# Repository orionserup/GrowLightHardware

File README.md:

# GrowLightHardware
 Hardware for the Open Source Grow Light

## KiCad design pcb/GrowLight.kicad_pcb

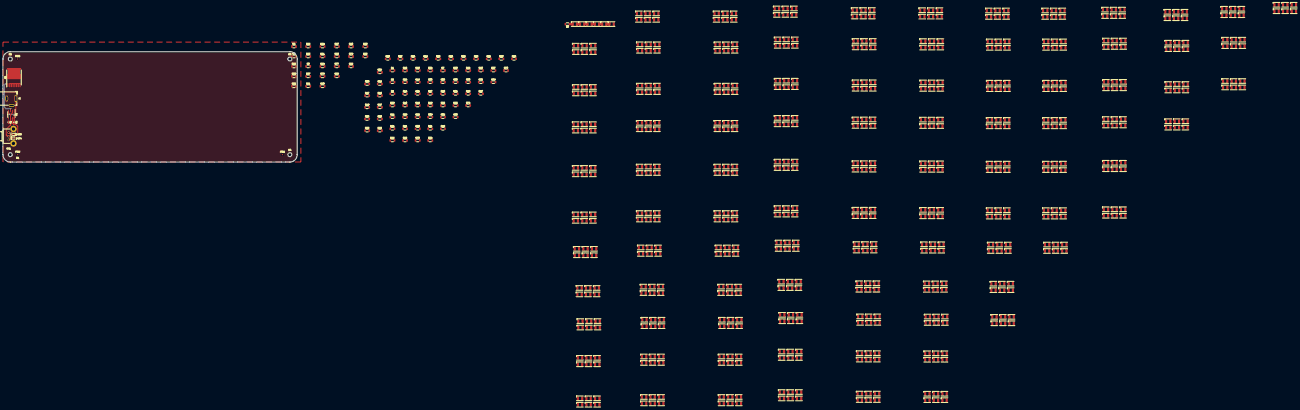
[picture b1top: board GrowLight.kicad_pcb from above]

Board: 2 copper layers, 203.2 x 76.2 mm, 687 parts (0 on the bottom side), 584 nets.

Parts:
C1: 100nF; C_0603_1608Metric
D1, D2, D3, D4, D5, D6, D7, D8, D9, D10, D11, D12, D13, D14, D15, D16, D17, D18, D19, D20, D21, D22, D23, D24, D25, D26, D27, D28, D29, D30, D31, D32, D33, D34, D35, D36, D37, D38, D39, D40, D41, D42, D43, D44, D45, D46, D47, D48, D49, D50, D51, D52, D53, D54, D55, D56, D57, D58, D59, D60, D61, D62, D63, D64, D65, D66, D67, D68, D69, D70, D71, D72, D73, D74, D75, D76, D77, D78, D79, D80, D81, D82, D83, D84, D85, D86, D87, D88, D89, D90, D91, D92, D93, D94, D95, D96, D97, D98, D99, D100, D101, D102, D103, D104, D105, D106, D107, D108, D109, D110, D111, D112, D113, D114, D115, D116, D117, D118, D119, D120, D121, D122, D123, D124, D125, D126, D127, D128, D129, D130, D131, D132, D133, D134, D135, D136, D137, D138, D139, D140, D141, D142, D143, D144, D145, D146, D147, D148, D149, D150, D151, D152, D153, D154, D155, D156, D157, D158, D159, D160, D161, D162, D163, D164, D165, D166, D167, D168, D169, D170, D171, D172, D173, D174, D175, D176, D177, D178, D179, D180, D181, D182, D183, D184, D185, D186, D187, D188, D189, D190, D191, D192, D193, D194, D195, D196, D197, D198, D199, D200, D201, D202, D203, D204, D205, D206, D207, D208, D209, D210, D211, D212, D213, D214, D215, D216, D217, D218, D219, D220, D221, D222, D223, D224, D225, D226, D227, D228, D229, D230, D231, D232, D233, D234, D235, D236, D237, D238, D239, D240, D241, D242, D243, D244, D245, D246, D247, D248, D249, D250, D251, D252, D253, D254, D255, D256, D257, D258, D259, D260, D261, D262, D263, D264, D265, D266, D267, D268, D269, D270, D271, D272, D273, D274, D275, D276, D277, D278, D279, D280, D281, D282, D283, D284, D285, D286, D287, D288, D289, D290, D291, D292, D293, D294, D295, D296, D297, D298, D299, D300, D301, D302, D303, D304, D305, D306, D307, D308, D309, D310, D311, D312, D313, D314, D315, D316, D317, D318, D319, D320, D321, D322, D323, D324, D325, D326, D327, D328, D329, D330, D331, D332, D333, D334, D335, D336, D337, D338, D339, D340, D341, D342, D343, D344, D345, D346, D347, D348, D349, D350, D351, D352, D353, D354, D355, D356, D357, D358, D359, D360, D361, D362, D363, D364, D365, D366, D367, D368, D369, D370, D371, D372, D373, D374, D375, D376, D377, D378, D379, D380, D381, D382, D383, D384, D385, D386, D387, D388, D389, D390, D391, D392, D393, D394, D395, D396, D397, D398, D399, D400, D401, D402, D403, D404, D405, D406, D407, D408, D409, D410, D411, D412, D413, D414, D415, D416, D417, D418, D419, D420, D421, D422, D423, D424, D425, D426, D427, D428, D429, D430, D431, D432, D435, D436, D437, D438, D439, D440, D441, D442, D443, D444, D445, D446, D447, D448, D449, D450, D451, D452, D453, D454, D455, D456, D457, D458, D459, D460, D461, D462, D463, D464, D465, D466, D467, D468, D469, D470, D471, D472, D473, D474, D475, D476, D477, D478, D479, D480, D481, D482, D483, D484, D485, D486, D487, D488, D489, D490, D491, D492, D493, D494, D495, D496, D497, D498, D499, D500, D501, D502, D503, D504, D505, D506, D507, D508, D509, D510, D511, D512, D513, D514, D515, D516, D517, D518, D519, D520, D521, D522, D523, D524, D525, D526, D527, D528, D529, D530, D531, D532, D533, D534, D535, D536, D537, D538, D539, D540, D541, D542, D543, D544, D545, D546, D547, D548, D549, D550, D551, D552, D553, D554, D555, D556, D557, D558, D559, D560, D561, D562, D563, D564, D565, D566, D567, D568, D569, D570, D571, D572, D573, D574, D575, D576, D577, D578: RED; LED_PLCC-2
D433: SD0603S040S0R2; D_0603_1608Metric
D434: D; D_0603_1608Metric
FID1, FID2, FID3: Fiducial; Fiducial_1mm_Mask2mm
H1, H2, H3, H4: MountingHole; MountingHole_2.7mm_M2.5_ISO7380
J1: Barrel_Jack; BarrelJack_GCT_DCJ200-10-A_Horizontal
Q1: IPT012N08N5; Infineon_PG-HSOF-8-1
R1, R3, R4, R5, R6, R7, R8, R9, R10, R11, R12, R13, R14, R15, R16, R17, R18, R19, R20, R21, R22, R23, R24, R25, R26, R27, R28, R29, R30, R31, R32, R33, R34, R35, R36, R37, R38, R39, R40, R41, R42, R43, R44, R45, R46, R47, R48, R49, R50, R51, R52, R53, R54, R55, R56, R57, R58, R59, R60, R61, R62, R63, R64, R65, R66, R67, R68, R69, R70, R71, R72, R73, R74, R75, R76, R77, R78, R79, R80, R81, R82, R83, R84, R85, R86, R87, R88, R89, R90, R91, R92, R93, R94, R95, R96, R97: 20; R_1206_3216Metric
R2: 1k; R_0603_1608Metric
RV1: 10k; Potentiometer_Bourns_PTV09A-2_Single_Horizontal
U1: LM555xM; SOIC-8_3.9x4.9mm_P1.27mm

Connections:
/Control Circuitry/CTRL: Q1.1 (G), U1.3 (Q)
/Control Circuitry/THR: C1.1, RV1.2, U1.2 (TR), U1.6 (THR)
/LED Grid/CATHODE: Q1.3 (D), R1.2, R3.2, R4.2, R5.2, R6.2, R7.2, R8.2, R9.2, R10.2, R11.2, R12.2, R13.2, R14.2, R15.2, R16.2, R17.2, R18.2, R19.2, R20.2, R21.2, R22.2, R23.2, R24.2, R25.2, R26.2, R27.2, R28.2, R29.2, R30.2, R31.2, R32.2, R33.2, R34.2, R35.2, R36.2, R37.2, R38.2, R39.2, R40.2, R41.2, R42.2, R43.2, R44.2, R45.2, R46.2, R47.2, R48.2, R49.2, R50.2, R51.2, R52.2, R53.2, R54.2, R55.2, R56.2, R57.2, R58.2, R59.2, R60.2, R61.2, R62.2, R63.2, R64.2, R65.2, R66.2, R67.2, R68.2, R69.2, R70.2, R71.2, R72.2, R73.2, R74.2, R75.2, R76.2, R77.2, R78.2, R79.2, R80.2, R81.2, R82.2, R83.2, R84.2, R85.2, R86.2, R87.2, R88.2, R89.2, R90.2, R91.2, R92.2, R93.2, R94.2, R95.2, R96.2, R97.2
/V_{LED}: D1.2 (A), D7.2 (A), D13.2 (A), D19.2 (A), D25.2 (A), D31.2 (A), D37.2 (A), D43.2 (A), D49.2 (A), D55.2 (A), D61.2 (A), D67.2 (A), D73.2 (A), D79.2 (A), D85.2 (A), D91.2 (A), D97.2 (A), D103.2 (A), D109.2 (A), D115.2 (A), D121.2 (A), D127.2 (A), D133.2 (A), D139.2 (A), D145.2 (A), D151.2 (A), D157.2 (A), D163.2 (A), D169.2 (A), D175.2 (A), D181.2 (A), D187.2 (A), D193.2 (A), D199.2 (A), D205.2 (A), D211.2 (A), D217.2 (A), D223.2 (A), D229.2 (A), D235.2 (A), D241.2 (A), D247.2 (A), D253.2 (A), D259.2 (A), D265.2 (A), D271.2 (A), D277.2 (A), D283.2 (A), D289.2 (A), D295.2 (A), D301.2 (A), D307.2 (A), D313.2 (A), D319.2 (A), D325.2 (A), D331.2 (A), D337.2 (A), D343.2 (A), D349.2 (A), D355.2 (A), D361.2 (A), D367.2 (A), D373.2 (A), D379.2 (A), D385.2 (A), D391.2 (A), D397.2 (A), D403.2 (A), D409.2 (A), D415.2 (A), D421.2 (A), D427.2 (A), D435.2 (A), D441.2 (A), D447.2 (A), D453.2 (A), D459.2 (A), D465.2 (A), D471.2 (A), D477.2 (A), D483.2 (A), D489.2 (A), D495.2 (A), D501.2 (A), D507.2 (A), D513.2 (A), D519.2 (A), D525.2 (A), D531.2 (A), D537.2 (A), D543.2 (A), D549.2 (A), D555.2 (A), D561.2 (A), D567.2 (A), D573.2 (A), J1.1, R2.1, U1.4 (R), U1.8 (VCC)
Earth: C1.2, J1.2, Q1.2 (S), U1.1 (GND)
unnamed: D1.1 (K), D2.2 (A)
unnamed: D2.1 (K), D3.2 (A)
unnamed: D3.1 (K), D4.2 (A)
unnamed: D4.1 (K), D5.2 (A)
unnamed: D5.1 (K), D6.2 (A)
unnamed: D6.1 (K), R1.1
unnamed: D7.1 (K), D8.2 (A)
unnamed: D8.1 (K), D9.2 (A)
unnamed: D10.1 (K), D11.2 (A)
unnamed: D9.1 (K), D10.2 (A)
unnamed: D11.1 (K), D12.2 (A)
unnamed: D12.1 (K), R3.1
unnamed: D13.1 (K), D14.2 (A)
unnamed: D14.1 (K), D15.2 (A)
unnamed: D15.1 (K), D16.2 (A)
unnamed: D16.1 (K), D17.2 (A)
unnamed: D17.1 (K), D18.2 (A)
unnamed: D18.1 (K), R4.1
unnamed: D19.1 (K), D20.2 (A)
unnamed: D20.1 (K), D21.2 (A)
unnamed: D21.1 (K), D22.2 (A)
unnamed: D22.1 (K), D23.2 (A)
unnamed: D23.1 (K), D24.2 (A)
unnamed: D24.1 (K), R5.1
unnamed: D25.1 (K), D26.2 (A)
unnamed: D26.1 (K), D27.2 (A)
unnamed: D27.1 (K), D28.2 (A)
unnamed: D28.1 (K), D29.2 (A)
unnamed: D29.1 (K), D30.2 (A)
unnamed: D30.1 (K), R6.1
unnamed: D31.1 (K), D32.2 (A)
unnamed: D32.1 (K), D33.2 (A)
unnamed: D33.1 (K), D34.2 (A)
unnamed: D34.1 (K), D35.2 (A)
unnamed: D35.1 (K), D36.2 (A)
unnamed: D36.1 (K), R7.1
unnamed: D37.1 (K), D38.2 (A)
unnamed: D38.1 (K), D39.2 (A)
unnamed: D39.1 (K), D40.2 (A)
unnamed: D40.1 (K), D41.2 (A)
unnamed: D41.1 (K), D42.2 (A)
unnamed: D42.1 (K), R8.1
unnamed: D43.1 (K), D44.2 (A)
unnamed: D44.1 (K), D45.2 (A)
unnamed: D45.1 (K), D46.2 (A)
unnamed: D46.1 (K), D47.2 (A)
unnamed: D47.1 (K), D48.2 (A)
unnamed: D48.1 (K), R9.1
unnamed: D49.1 (K), D50.2 (A)
unnamed: D50.1 (K), D51.2 (A)
unnamed: D51.1 (K), D52.2 (A)
unnamed: D52.1 (K), D53.2 (A)
unnamed: D53.1 (K), D54.2 (A)
unnamed: D54.1 (K), R10.1
unnamed: D55.1 (K), D56.2 (A)
unnamed: D56.1 (K), D57.2 (A)
unnamed: D57.1 (K), D58.2 (A)
unnamed: D58.1 (K), D59.2 (A)
unnamed: D59.1 (K), D60.2 (A)
unnamed: D60.1 (K), R11.1
unnamed: D61.1 (K), D62.2 (A)
unnamed: D62.1 (K), D63.2 (A)
unnamed: D63.1 (K), D64.2 (A)
unnamed: D64.1 (K), D65.2 (A)
unnamed: D65.1 (K), D66.2 (A)
unnamed: D66.1 (K), R12.1
unnamed: D67.1 (K), D68.2 (A)
unnamed: D68.1 (K), D69.2 (A)
unnamed: D69.1 (K), D70.2 (A)
unnamed: D70.1 (K), D71.2 (A)
unnamed: D71.1 (K), D72.2 (A)
unnamed: D72.1 (K), R13.1
unnamed: D73.1 (K), D74.2 (A)
unnamed: D74.1 (K), D75.2 (A)
unnamed: D75.1 (K), D76.2 (A)
unnamed: D76.1 (K), D77.2 (A)
unnamed: D77.1 (K), D78.2 (A)
unnamed: D78.1 (K), R14.1
unnamed: D79.1 (K), D80.2 (A)
unnamed: D80.1 (K), D81.2 (A)
unnamed: D81.1 (K), D82.2 (A)
unnamed: D82.1 (K), D83.2 (A)
unnamed: D83.1 (K), D84.2 (A)
unnamed: D84.1 (K), R15.1
unnamed: D85.1 (K), D86.2 (A)
unnamed: D86.1 (K), D87.2 (A)
unnamed: D87.1 (K), D88.2 (A)
unnamed: D88.1 (K), D89.2 (A)
unnamed: D89.1 (K), D90.2 (A)
unnamed: D90.1 (K), R16.1
unnamed: D91.1 (K), D92.2 (A)
unnamed: D92.1 (K), D93.2 (A)
unnamed: D93.1 (K), D94.2 (A)
unnamed: D94.1 (K), D95.2 (A)
unnamed: D95.1 (K), D96.2 (A)
unnamed: D96.1 (K), R17.1
unnamed: D97.1 (K), D98.2 (A)
unnamed: D98.1 (K), D99.2 (A)
unnamed: D100.1 (K), D101.2 (A)
unnamed: D99.1 (K), D100.2 (A)
unnamed: D101.1 (K), D102.2 (A)
unnamed: D102.1 (K), R18.1
unnamed: D103.1 (K), D104.2 (A)
unnamed: D104.1 (K), D105.2 (A)
unnamed: D105.1 (K), D106.2 (A)
unnamed: D106.1 (K), D107.2 (A)
unnamed: D107.1 (K), D108.2 (A)
unnamed: D108.1 (K), R19.1
unnamed: D109.1 (K), D110.2 (A)
unnamed: D110.1 (K), D111.2 (A)
unnamed: D111.1 (K), D112.2 (A)
unnamed: D112.1 (K), D113.2 (A)
unnamed: D113.1 (K), D114.2 (A)
unnamed: D114.1 (K), R20.1
unnamed: D115.1 (K), D116.2 (A)
unnamed: D116.1 (K), D117.2 (A)
unnamed: D117.1 (K), D118.2 (A)
unnamed: D118.1 (K), D119.2 (A)
unnamed: D119.1 (K), D120.2 (A)
unnamed: D120.1 (K), R21.1
unnamed: D121.1 (K), D122.2 (A)
unnamed: D122.1 (K), D123.2 (A)
unnamed: D123.1 (K), D124.2 (A)
unnamed: D124.1 (K), D125.2 (A)
unnamed: D125.1 (K), D126.2 (A)
unnamed: D126.1 (K), R22.1
unnamed: D127.1 (K), D128.2 (A)
unnamed: D128.1 (K), D129.2 (A)
unnamed: D129.1 (K), D130.2 (A)
unnamed: D130.1 (K), D131.2 (A)
unnamed: D131.1 (K), D132.2 (A)
unnamed: D132.1 (K), R23.1
unnamed: D133.1 (K), D134.2 (A)
unnamed: D134.1 (K), D135.2 (A)
unnamed: D135.1 (K), D136.2 (A)
unnamed: D136.1 (K), D137.2 (A)
unnamed: D137.1 (K), D138.2 (A)
unnamed: D138.1 (K), R24.1
unnamed: D139.1 (K), D140.2 (A)
unnamed: D140.1 (K), D141.2 (A)
unnamed: D141.1 (K), D142.2 (A)
unnamed: D142.1 (K), D143.2 (A)
unnamed: D143.1 (K), D144.2 (A)
unnamed: D144.1 (K), R25.1
unnamed: D145.1 (K), D146.2 (A)
unnamed: D146.1 (K), D147.2 (A)
unnamed: D147.1 (K), D148.2 (A)
unnamed: D148.1 (K), D149.2 (A)
unnamed: D149.1 (K), D150.2 (A)
unnamed: D150.1 (K), R26.1
unnamed: D151.1 (K), D152.2 (A)
unnamed: D152.1 (K), D153.2 (A)
unnamed: D153.1 (K), D154.2 (A)
unnamed: D154.1 (K), D155.2 (A)
unnamed: D155.1 (K), D156.2 (A)
unnamed: D156.1 (K), R27.1
unnamed: D157.1 (K), D158.2 (A)
unnamed: D158.1 (K), D159.2 (A)
unnamed: D159.1 (K), D160.2 (A)
unnamed: D160.1 (K), D161.2 (A)
unnamed: D161.1 (K), D162.2 (A)
unnamed: D162.1 (K), R28.1
unnamed: D163.1 (K), D164.2 (A)
unnamed: D164.1 (K), D165.2 (A)
unnamed: D165.1 (K), D166.2 (A)
unnamed: D166.1 (K), D167.2 (A)
unnamed: D167.1 (K), D168.2 (A)
unnamed: D168.1 (K), R29.1
unnamed: D169.1 (K), D170.2 (A)
unnamed: D170.1 (K), D171.2 (A)
unnamed: D171.1 (K), D172.2 (A)
unnamed: D172.1 (K), D173.2 (A)
unnamed: D173.1 (K), D174.2 (A)
unnamed: D174.1 (K), R30.1
unnamed: D175.1 (K), D176.2 (A)
unnamed: D176.1 (K), D177.2 (A)
unnamed: D177.1 (K), D178.2 (A)
unnamed: D178.1 (K), D179.2 (A)
unnamed: D179.1 (K), D180.2 (A)
unnamed: D180.1 (K), R31.1
unnamed: D181.1 (K), D182.2 (A)
unnamed: D182.1 (K), D183.2 (A)
unnamed: D183.1 (K), D184.2 (A)
unnamed: D184.1 (K), D185.2 (A)
unnamed: D185.1 (K), D186.2 (A)
unnamed: D186.1 (K), R32.1
unnamed: D187.1 (K), D188.2 (A)
unnamed: D188.1 (K), D189.2 (A)
unnamed: D189.1 (K), D190.2 (A)
unnamed: D190.1 (K), D191.2 (A)
unnamed: D191.1 (K), D192.2 (A)
unnamed: D192.1 (K), R33.1
unnamed: D193.1 (K), D194.2 (A)
unnamed: D194.1 (K), D195.2 (A)
unnamed: D195.1 (K), D196.2 (A)
unnamed: D196.1 (K), D197.2 (A)
unnamed: D197.1 (K), D198.2 (A)
unnamed: D198.1 (K), R34.1
unnamed: D199.1 (K), D200.2 (A)
unnamed: D200.1 (K), D201.2 (A)
unnamed: D201.1 (K), D202.2 (A)
unnamed: D202.1 (K), D203.2 (A)
unnamed: D203.1 (K), D204.2 (A)
unnamed: D204.1 (K), R35.1
unnamed: D205.1 (K), D206.2 (A)
unnamed: D206.1 (K), D207.2 (A)
unnamed: D207.1 (K), D208.2 (A)
unnamed: D208.1 (K), D209.2 (A)
unnamed: D209.1 (K), D210.2 (A)
unnamed: D210.1 (K), R36.1
unnamed: D211.1 (K), D212.2 (A)
unnamed: D212.1 (K), D213.2 (A)
unnamed: D213.1 (K), D214.2 (A)
unnamed: D214.1 (K), D215.2 (A)
unnamed: D215.1 (K), D216.2 (A)
unnamed: D216.1 (K), R37.1
unnamed: D217.1 (K), D218.2 (A)
unnamed: D218.1 (K), D219.2 (A)
unnamed: D219.1 (K), D220.2 (A)
unnamed: D220.1 (K), D221.2 (A)
unnamed: D221.1 (K), D222.2 (A)
unnamed: D222.1 (K), R38.1
unnamed: D223.1 (K), D224.2 (A)
unnamed: D224.1 (K), D225.2 (A)
unnamed: D225.1 (K), D226.2 (A)
unnamed: D226.1 (K), D227.2 (A)
unnamed: D227.1 (K), D228.2 (A)
unnamed: D228.1 (K), R39.1
unnamed: D229.1 (K), D230.2 (A)
unnamed: D230.1 (K), D231.2 (A)
unnamed: D231.1 (K), D232.2 (A)
unnamed: D232.1 (K), D233.2 (A)
unnamed: D233.1 (K), D234.2 (A)
unnamed: D234.1 (K), R40.1
unnamed: D235.1 (K), D236.2 (A)
unnamed: D236.1 (K), D237.2 (A)
unnamed: D237.1 (K), D238.2 (A)
unnamed: D238.1 (K), D239.2 (A)
unnamed: D239.1 (K), D240.2 (A)
unnamed: D240.1 (K), R41.1
unnamed: D241.1 (K), D242.2 (A)
unnamed: D242.1 (K), D243.2 (A)
unnamed: D243.1 (K), D244.2 (A)
unnamed: D244.1 (K), D245.2 (A)
unnamed: D245.1 (K), D246.2 (A)
unnamed: D246.1 (K), R42.1
unnamed: D247.1 (K), D248.2 (A)
unnamed: D248.1 (K), D249.2 (A)
unnamed: D249.1 (K), D250.2 (A)
unnamed: D250.1 (K), D251.2 (A)
unnamed: D251.1 (K), D252.2 (A)
unnamed: D252.1 (K), R43.1
unnamed: D253.1 (K), D254.2 (A)
unnamed: D254.1 (K), D255.2 (A)
unnamed: D255.1 (K), D256.2 (A)
unnamed: D256.1 (K), D257.2 (A)
unnamed: D257.1 (K), D258.2 (A)
unnamed: D258.1 (K), R44.1
unnamed: D259.1 (K), D260.2 (A)
unnamed: D260.1 (K), D261.2 (A)
unnamed: D261.1 (K), D262.2 (A)
unnamed: D262.1 (K), D263.2 (A)
unnamed: D263.1 (K), D264.2 (A)
unnamed: D264.1 (K), R45.1
unnamed: D265.1 (K), D266.2 (A)
unnamed: D266.1 (K), D267.2 (A)
unnamed: D267.1 (K), D268.2 (A)
unnamed: D268.1 (K), D269.2 (A)
unnamed: D269.1 (K), D270.2 (A)
unnamed: D270.1 (K), R46.1
unnamed: D271.1 (K), D272.2 (A)
unnamed: D272.1 (K), D273.2 (A)
unnamed: D273.1 (K), D274.2 (A)
unnamed: D274.1 (K), D275.2 (A)
unnamed: D275.1 (K), D276.2 (A)
unnamed: D276.1 (K), R47.1
unnamed: D277.1 (K), D278.2 (A)
unnamed: D278.1 (K), D279.2 (A)
unnamed: D279.1 (K), D280.2 (A)
unnamed: D280.1 (K), D281.2 (A)
unnamed: D281.1 (K), D282.2 (A)
unnamed: D282.1 (K), R48.1
unnamed: D283.1 (K), D284.2 (A)
unnamed: D284.1 (K), D285.2 (A)
unnamed: D285.1 (K), D286.2 (A)
unnamed: D286.1 (K), D287.2 (A)
unnamed: D287.1 (K), D288.2 (A)
unnamed: D288.1 (K), R49.1
unnamed: D289.1 (K), D290.2 (A)
unnamed: D290.1 (K), D291.2 (A)
unnamed: D291.1 (K), D292.2 (A)
unnamed: D292.1 (K), D293.2 (A)
unnamed: D293.1 (K), D294.2 (A)
unnamed: D294.1 (K), R50.1
unnamed: D295.1 (K), D296.2 (A)
unnamed: D296.1 (K), D297.2 (A)
unnamed: D297.1 (K), D298.2 (A)
unnamed: D298.1 (K), D299.2 (A)
unnamed: D299.1 (K), D300.2 (A)
unnamed: D300.1 (K), R51.1
unnamed: D301.1 (K), D302.2 (A)
unnamed: D302.1 (K), D303.2 (A)
unnamed: D303.1 (K), D304.2 (A)
unnamed: D304.1 (K), D305.2 (A)
unnamed: D305.1 (K), D306.2 (A)
unnamed: D306.1 (K), R52.1
unnamed: D307.1 (K), D308.2 (A)
unnamed: D308.1 (K), D309.2 (A)
unnamed: D309.1 (K), D310.2 (A)
unnamed: D310.1 (K), D311.2 (A)
unnamed: D311.1 (K), D312.2 (A)
unnamed: D312.1 (K), R53.1
unnamed: D313.1 (K), D314.2 (A)
unnamed: D314.1 (K), D315.2 (A)
unnamed: D315.1 (K), D316.2 (A)
unnamed: D316.1 (K), D317.2 (A)
unnamed: D317.1 (K), D318.2 (A)
unnamed: D318.1 (K), R54.1
unnamed: D319.1 (K), D320.2 (A)
unnamed: D320.1 (K), D321.2 (A)
unnamed: D321.1 (K), D322.2 (A)
unnamed: D322.1 (K), D323.2 (A)
unnamed: D323.1 (K), D324.2 (A)
unnamed: D324.1 (K), R55.1
unnamed: D325.1 (K), D326.2 (A)
unnamed: D326.1 (K), D327.2 (A)
unnamed: D327.1 (K), D328.2 (A)
unnamed: D328.1 (K), D329.2 (A)
unnamed: D329.1 (K), D330.2 (A)
unnamed: D330.1 (K), R56.1
unnamed: D331.1 (K), D332.2 (A)
unnamed: D332.1 (K), D333.2 (A)
unnamed: D333.1 (K), D334.2 (A)
unnamed: D334.1 (K), D335.2 (A)
unnamed: D335.1 (K), D336.2 (A)
unnamed: D336.1 (K), R57.1
unnamed: D337.1 (K), D338.2 (A)
unnamed: D338.1 (K), D339.2 (A)
unnamed: D339.1 (K), D340.2 (A)
unnamed: D340.1 (K), D341.2 (A)
unnamed: D341.1 (K), D342.2 (A)
unnamed: D342.1 (K), R58.1
unnamed: D343.1 (K), D344.2 (A)
unnamed: D344.1 (K), D345.2 (A)
unnamed: D345.1 (K), D346.2 (A)
unnamed: D346.1 (K), D347.2 (A)
unnamed: D347.1 (K), D348.2 (A)
unnamed: D348.1 (K), R59.1
unnamed: D349.1 (K), D350.2 (A)
unnamed: D350.1 (K), D351.2 (A)
unnamed: D351.1 (K), D352.2 (A)
unnamed: D352.1 (K), D353.2 (A)
unnamed: D353.1 (K), D354.2 (A)
unnamed: D354.1 (K), R60.1
unnamed: D355.1 (K), D356.2 (A)
unnamed: D356.1 (K), D357.2 (A)
unnamed: D357.1 (K), D358.2 (A)
unnamed: D358.1 (K), D359.2 (A)
unnamed: D359.1 (K), D360.2 (A)
unnamed: D360.1 (K), R61.1
unnamed: D361.1 (K), D362.2 (A)
unnamed: D362.1 (K), D363.2 (A)
unnamed: D363.1 (K), D364.2 (A)
unnamed: D364.1 (K), D365.2 (A)
unnamed: D365.1 (K), D366.2 (A)
unnamed: D366.1 (K), R62.1
unnamed: D367.1 (K), D368.2 (A)
unnamed: D368.1 (K), D369.2 (A)
unnamed: D369.1 (K), D370.2 (A)
unnamed: D370.1 (K), D371.2 (A)
unnamed: D371.1 (K), D372.2 (A)
unnamed: D372.1 (K), R63.1
unnamed: D373.1 (K), D374.2 (A)
unnamed: D374.1 (K), D375.2 (A)
unnamed: D375.1 (K), D376.2 (A)
unnamed: D376.1 (K), D377.2 (A)
unnamed: D377.1 (K), D378.2 (A)
unnamed: D378.1 (K), R64.1
unnamed: D379.1 (K), D380.2 (A)
unnamed: D380.1 (K), D381.2 (A)
unnamed: D381.1 (K), D382.2 (A)
unnamed: D382.1 (K), D383.2 (A)
unnamed: D383.1 (K), D384.2 (A)
unnamed: D384.1 (K), R65.1
unnamed: D385.1 (K), D386.2 (A)
unnamed: D386.1 (K), D387.2 (A)
unnamed: D387.1 (K), D388.2 (A)
unnamed: D388.1 (K), D389.2 (A)
unnamed: D389.1 (K), D390.2 (A)
unnamed: D390.1 (K), R66.1
unnamed: D391.1 (K), D392.2 (A)
unnamed: D392.1 (K), D393.2 (A)
unnamed: D393.1 (K), D394.2 (A)
unnamed: D394.1 (K), D395.2 (A)
unnamed: D395.1 (K), D396.2 (A)
unnamed: D396.1 (K), R67.1
unnamed: D397.1 (K), D398.2 (A)
unnamed: D398.1 (K), D399.2 (A)
unnamed: D399.1 (K), D400.2 (A)
unnamed: D400.1 (K), D401.2 (A)
unnamed: D401.1 (K), D402.2 (A)
unnamed: D402.1 (K), R68.1
unnamed: D403.1 (K), D404.2 (A)
unnamed: D404.1 (K), D405.2 (A)
unnamed: D405.1 (K), D406.2 (A)
unnamed: D406.1 (K), D407.2 (A)
unnamed: D407.1 (K), D408.2 (A)
unnamed: D408.1 (K), R69.1
unnamed: D409.1 (K), D410.2 (A)
unnamed: D410.1 (K), D411.2 (A)
unnamed: D411.1 (K), D412.2 (A)
unnamed: D412.1 (K), D413.2 (A)
unnamed: D413.1 (K), D414.2 (A)
unnamed: D414.1 (K), R70.1
unnamed: D415.1 (K), D416.2 (A)
unnamed: D416.1 (K), D417.2 (A)
unnamed: D417.1 (K), D418.2 (A)
unnamed: D418.1 (K), D419.2 (A)
unnamed: D419.1 (K), D420.2 (A)
unnamed: D420.1 (K), R71.1
unnamed: D421.1 (K), D422.2 (A)
unnamed: D422.1 (K), D423.2 (A)
unnamed: D423.1 (K), D424.2 (A)
unnamed: D424.1 (K), D425.2 (A)
unnamed: D425.1 (K), D426.2 (A)
unnamed: D426.1 (K), R72.1
unnamed: D427.1 (K), D428.2 (A)
unnamed: D428.1 (K), D429.2 (A)
unnamed: D429.1 (K), D430.2 (A)
unnamed: D430.1 (K), D431.2 (A)
unnamed: D431.1 (K), D432.2 (A)
unnamed: D432.1 (K), R73.1
unnamed: D433.1 (K), RV1.3
unnamed: D433.2 (A), D434.1 (K), R2.2, U1.7 (DIS)
unnamed: D434.2 (A), RV1.1
unnamed: D435.1 (K), D436.2 (A)
unnamed: D436.1 (K), D437.2 (A)
unnamed: D437.1 (K), D438.2 (A)
unnamed: D438.1 (K), D439.2 (A)
unnamed: D439.1 (K), D440.2 (A)
unnamed: D440.1 (K), R74.1
unnamed: D441.1 (K), D442.2 (A)
unnamed: D442.1 (K), D443.2 (A)
unnamed: D443.1 (K), D444.2 (A)
unnamed: D444.1 (K), D445.2 (A)
unnamed: D445.1 (K), D446.2 (A)
unnamed: D446.1 (K), R75.1
unnamed: D447.1 (K), D448.2 (A)
unnamed: D448.1 (K), D449.2 (A)
unnamed: D449.1 (K), D450.2 (A)
unnamed: D450.1 (K), D451.2 (A)
unnamed: D451.1 (K), D452.2 (A)
unnamed: D452.1 (K), R76.1
unnamed: D453.1 (K), D454.2 (A)
unnamed: D454.1 (K), D455.2 (A)
unnamed: D455.1 (K), D456.2 (A)
unnamed: D456.1 (K), D457.2 (A)
unnamed: D457.1 (K), D458.2 (A)
unnamed: D458.1 (K), R77.1
unnamed: D459.1 (K), D460.2 (A)
unnamed: D460.1 (K), D461.2 (A)
unnamed: D461.1 (K), D462.2 (A)
unnamed: D462.1 (K), D463.2 (A)
unnamed: D463.1 (K), D464.2 (A)
unnamed: D464.1 (K), R78.1
unnamed: D465.1 (K), D466.2 (A)
unnamed: D466.1 (K), D467.2 (A)
unnamed: D467.1 (K), D468.2 (A)
unnamed: D468.1 (K), D469.2 (A)
unnamed: D469.1 (K), D470.2 (A)
unnamed: D470.1 (K), R79.1
unnamed: D471.1 (K), D472.2 (A)
unnamed: D472.1 (K), D473.2 (A)
unnamed: D473.1 (K), D474.2 (A)
unnamed: D474.1 (K), D475.2 (A)
unnamed: D475.1 (K), D476.2 (A)
unnamed: D476.1 (K), R80.1
unnamed: D477.1 (K), D478.2 (A)
unnamed: D478.1 (K), D479.2 (A)
unnamed: D479.1 (K), D480.2 (A)
unnamed: D480.1 (K), D481.2 (A)
unnamed: D481.1 (K), D482.2 (A)
unnamed: D482.1 (K), R81.1
unnamed: D483.1 (K), D484.2 (A)
unnamed: D484.1 (K), D485.2 (A)
unnamed: D485.1 (K), D486.2 (A)
unnamed: D486.1 (K), D487.2 (A)
unnamed: D487.1 (K), D488.2 (A)
unnamed: D488.1 (K), R82.1
unnamed: D489.1 (K), D490.2 (A)
unnamed: D490.1 (K), D491.2 (A)
unnamed: D491.1 (K), D492.2 (A)
unnamed: D492.1 (K), D493.2 (A)
unnamed: D493.1 (K), D494.2 (A)
unnamed: D494.1 (K), R83.1
unnamed: D495.1 (K), D496.2 (A)
unnamed: D496.1 (K), D497.2 (A)
unnamed: D497.1 (K), D498.2 (A)
unnamed: D498.1 (K), D499.2 (A)
unnamed: D499.1 (K), D500.2 (A)
unnamed: D500.1 (K), R84.1
unnamed: D501.1 (K), D502.2 (A)
unnamed: D502.1 (K), D503.2 (A)
unnamed: D503.1 (K), D504.2 (A)
unnamed: D504.1 (K), D505.2 (A)
unnamed: D505.1 (K), D506.2 (A)
unnamed: D506.1 (K), R85.1
unnamed: D507.1 (K), D508.2 (A)
unnamed: D508.1 (K), D509.2 (A)
unnamed: D509.1 (K), D510.2 (A)
unnamed: D510.1 (K), D511.2 (A)
unnamed: D511.1 (K), D512.2 (A)
unnamed: D512.1 (K), R86.1
unnamed: D513.1 (K), D514.2 (A)
unnamed: D514.1 (K), D515.2 (A)
unnamed: D515.1 (K), D516.2 (A)
unnamed: D516.1 (K), D517.2 (A)
unnamed: D517.1 (K), D518.2 (A)
unnamed: D518.1 (K), R87.1
unnamed: D519.1 (K), D520.2 (A)
unnamed: D520.1 (K), D521.2 (A)
unnamed: D521.1 (K), D522.2 (A)
unnamed: D522.1 (K), D523.2 (A)
unnamed: D523.1 (K), D524.2 (A)
unnamed: D524.1 (K), R88.1
unnamed: D525.1 (K), D526.2 (A)
unnamed: D526.1 (K), D527.2 (A)
unnamed: D527.1 (K), D528.2 (A)
unnamed: D528.1 (K), D529.2 (A)
unnamed: D529.1 (K), D530.2 (A)
unnamed: D530.1 (K), R89.1
unnamed: D531.1 (K), D532.2 (A)
unnamed: D532.1 (K), D533.2 (A)
unnamed: D533.1 (K), D534.2 (A)
unnamed: D534.1 (K), D535.2 (A)
unnamed: D535.1 (K), D536.2 (A)
unnamed: D536.1 (K), R90.1
unnamed: D537.1 (K), D538.2 (A)
unnamed: D538.1 (K), D539.2 (A)
unnamed: D539.1 (K), D540.2 (A)
unnamed: D540.1 (K), D541.2 (A)
unnamed: D541.1 (K), D542.2 (A)
unnamed: D542.1 (K), R91.1
unnamed: D543.1 (K), D544.2 (A)
unnamed: D544.1 (K), D545.2 (A)
unnamed: D545.1 (K), D546.2 (A)
unnamed: D546.1 (K), D547.2 (A)
unnamed: D547.1 (K), D548.2 (A)
unnamed: D548.1 (K), R92.1
unnamed: D549.1 (K), D550.2 (A)
unnamed: D550.1 (K), D551.2 (A)
unnamed: D551.1 (K), D552.2 (A)
unnamed: D552.1 (K), D553.2 (A)
unnamed: D553.1 (K), D554.2 (A)
unnamed: D554.1 (K), R93.1
unnamed: D555.1 (K), D556.2 (A)
unnamed: D556.1 (K), D557.2 (A)
unnamed: D557.1 (K), D558.2 (A)
unnamed: D558.1 (K), D559.2 (A)
unnamed: D559.1 (K), D560.2 (A)
unnamed: D560.1 (K), R94.1
unnamed: D561.1 (K), D562.2 (A)
unnamed: D562.1 (K), D563.2 (A)
unnamed: D563.1 (K), D564.2 (A)
unnamed: D564.1 (K), D565.2 (A)
unnamed: D565.1 (K), D566.2 (A)
unnamed: D566.1 (K), R95.1
unnamed: D567.1 (K), D568.2 (A)
unnamed: D568.1 (K), D569.2 (A)
unnamed: D569.1 (K), D570.2 (A)
unnamed: D570.1 (K), D571.2 (A)
unnamed: D571.1 (K), D572.2 (A)
unnamed: D572.1 (K), R96.1
unnamed: D573.1 (K), D574.2 (A)
unnamed: D574.1 (K), D575.2 (A)
unnamed: D575.1 (K), D576.2 (A)
unnamed: D576.1 (K), D577.2 (A)
unnamed: D577.1 (K), D578.2 (A)
unnamed: D578.1 (K), R97.1

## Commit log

2023-01-28 updates
    added circuitry
2023-02-01 finished design
2023-02-07 fixes
2023-02-07 Finished Rev 2
2023-02-07 added images
2023-02-11 Updated Dimensions
2023-03-18 Added BOM
2023-03-18 Updated Diode Name
